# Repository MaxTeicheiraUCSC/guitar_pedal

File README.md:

# guitar_pedal — DSP multi-effect (tremolo · delay · reverb · fuzz)

Daisy Seed3 + ESP32-C3 stereo pedal with a reorderable four-effect chain, five
momentary footswitches, a shared six-knob bank, global high/low-cut toggles, and
BLE-MIDI / WiFi web-UI control. Design rationale, research and the phased plan are
in [`docs/design.md`](docs/design.md); the control protocol in [`docs/midi-map.md`](docs/midi-map.md).

```
firmware/dsp/      portable DSP core (header-only C++17) — shared by the pedal and the emulator
firmware/daisy/    Seed3 wrapper: audio callback, switches, knobs, UART-MIDI, presets   [unverified: no ARM toolchain here]
firmware/esp32/    C3 bridge: BLE-MIDI + WiFi AP web UI ⇄ UART-MIDI                   [unverified: no ESP toolchain here]
web/               single-file web UI served by the ESP32
emulator/          macOS emulator: `emu` offline CLI, hardware model, JUCE front panel (Standalone + VST3), tests
hardware/spice/    ngspice reference of the Seed3 instrument I/O stages + validation harness
hardware/kicad/    carrier board (not started)
docs/              design.md, midi-map.md
```

## Build & test (macOS)

```sh
cd emulator && cmake -B build -DCMAKE_BUILD_TYPE=Release && cmake --build build -j8
./build/dsp_tests                                   # 45 property tests
./build/emu --list                                  # parameter tables + CC numbers
./build/emu --in guitar.wav --out fx.wav --enable 0,1,2,3 --order 3,0,1,2 --hw --cpu
cmake -B build-juce -DPEDAL_BUILD_JUCE=ON && cmake --build build-juce -j8   # JUCE app + VST3 (fetches JUCE 8.0.9)
cmake -B build-juce -DPEDAL_BUILD_JUCE=ON -DPEDAL_HARNESS=ON && ./build-juce/juce/PedalHarness_artefacts/Release/PedalHarness   # in-process UI/audio stress test
cd ../hardware/spice/validate && python3 run_all.py # simple model vs ngspice → out/report.md
```

Handover: **[`docs/STATUS.md`](docs/STATUS.md)** (what is and is not verified, next steps) and
**[`docs/LEARNINGS.md`](docs/LEARNINGS.md)** (the non-obvious things this cost time to find).

## Status (2026-09-22)

- DSP core, emulator CLI, property tests, SPICE reference and validation harness: **done and passing**.
- Validation found and fixed a real error in the hand-derived analog model (input gain −6.2 dB, not −4.6 dB)
  and shows the codec's ±1.8 V limit is reached at ≈3.7 V pk at the jack, before the op-amps clip
  → the carrier board gets Schottky clamps at the codec input.
- JUCE front panel: builds Standalone + VST3 (AU needs full Xcode). Default source is an embedded CC0 clean-guitar loop (`emulator/assets`), so no interface is needed to audition; live input is a menu choice. `PedalHarness` drives the real processor + editor with concurrent audio at 44.1/48/96 kHz and passes.
- Daisy / ESP32 firmware: written, **not compiled** (toolchains not installed on this machine).
- KiCad carrier board: generated from one netlist, routed, 0 DRC errors with schematic parity; gerbers/STEP/BOM in `hardware/kicad/out/`.
- Windows VST3 v0.1.3 links the CRT statically and ships an installer — earlier builds needed the VC++ redistributable and failed to load without it.
- Hardware: nothing fabricated. First hardware task is the Phase A bench measurement in `docs/design.md` §11.
- A project guard (`.claude/settings.json` + `.claude/hooks/guard.py`) confines Claude Code sessions in this repo to this repo; see `docs/STATUS.md`.

## Windows / macOS binaries

`.github/workflows/build.yml` builds the emulator on `windows-latest` (MSVC) and `macos-latest`, runs the
DSP tests, and uploads `PedalEmu-windows-x64.zip` (installer + PedalEmu.vst3 + standalone) and the setup .exe and `PedalEmu-macos.zip`
as workflow artifacts; pushing a tag `v*` publishes them as a GitHub Release. Windows install/troubleshooting: `docs/WINDOWS-INSTALL.md`. The Windows job also builds an
Inno Setup installer, checks the binaries have no dynamic MSVC-runtime dependency, and re-validates
the plugin after extracting the shipped zip. Local Windows build:
`cd emulator && cmake -B build -DPEDAL_BUILD_JUCE=ON && cmake --build build --config Release --target PedalEmu_Standalone PedalEmu_VST3`
(Visual Studio 2022 Build Tools; JUCE 8.0.9 is fetched by CMake). The Windows build has only been
exercised in CI — see the Actions tab for the current status.

License: GPLv3 (see `LICENSE`) — this is the free JUCE tier and permits the GPL reverb algorithms.

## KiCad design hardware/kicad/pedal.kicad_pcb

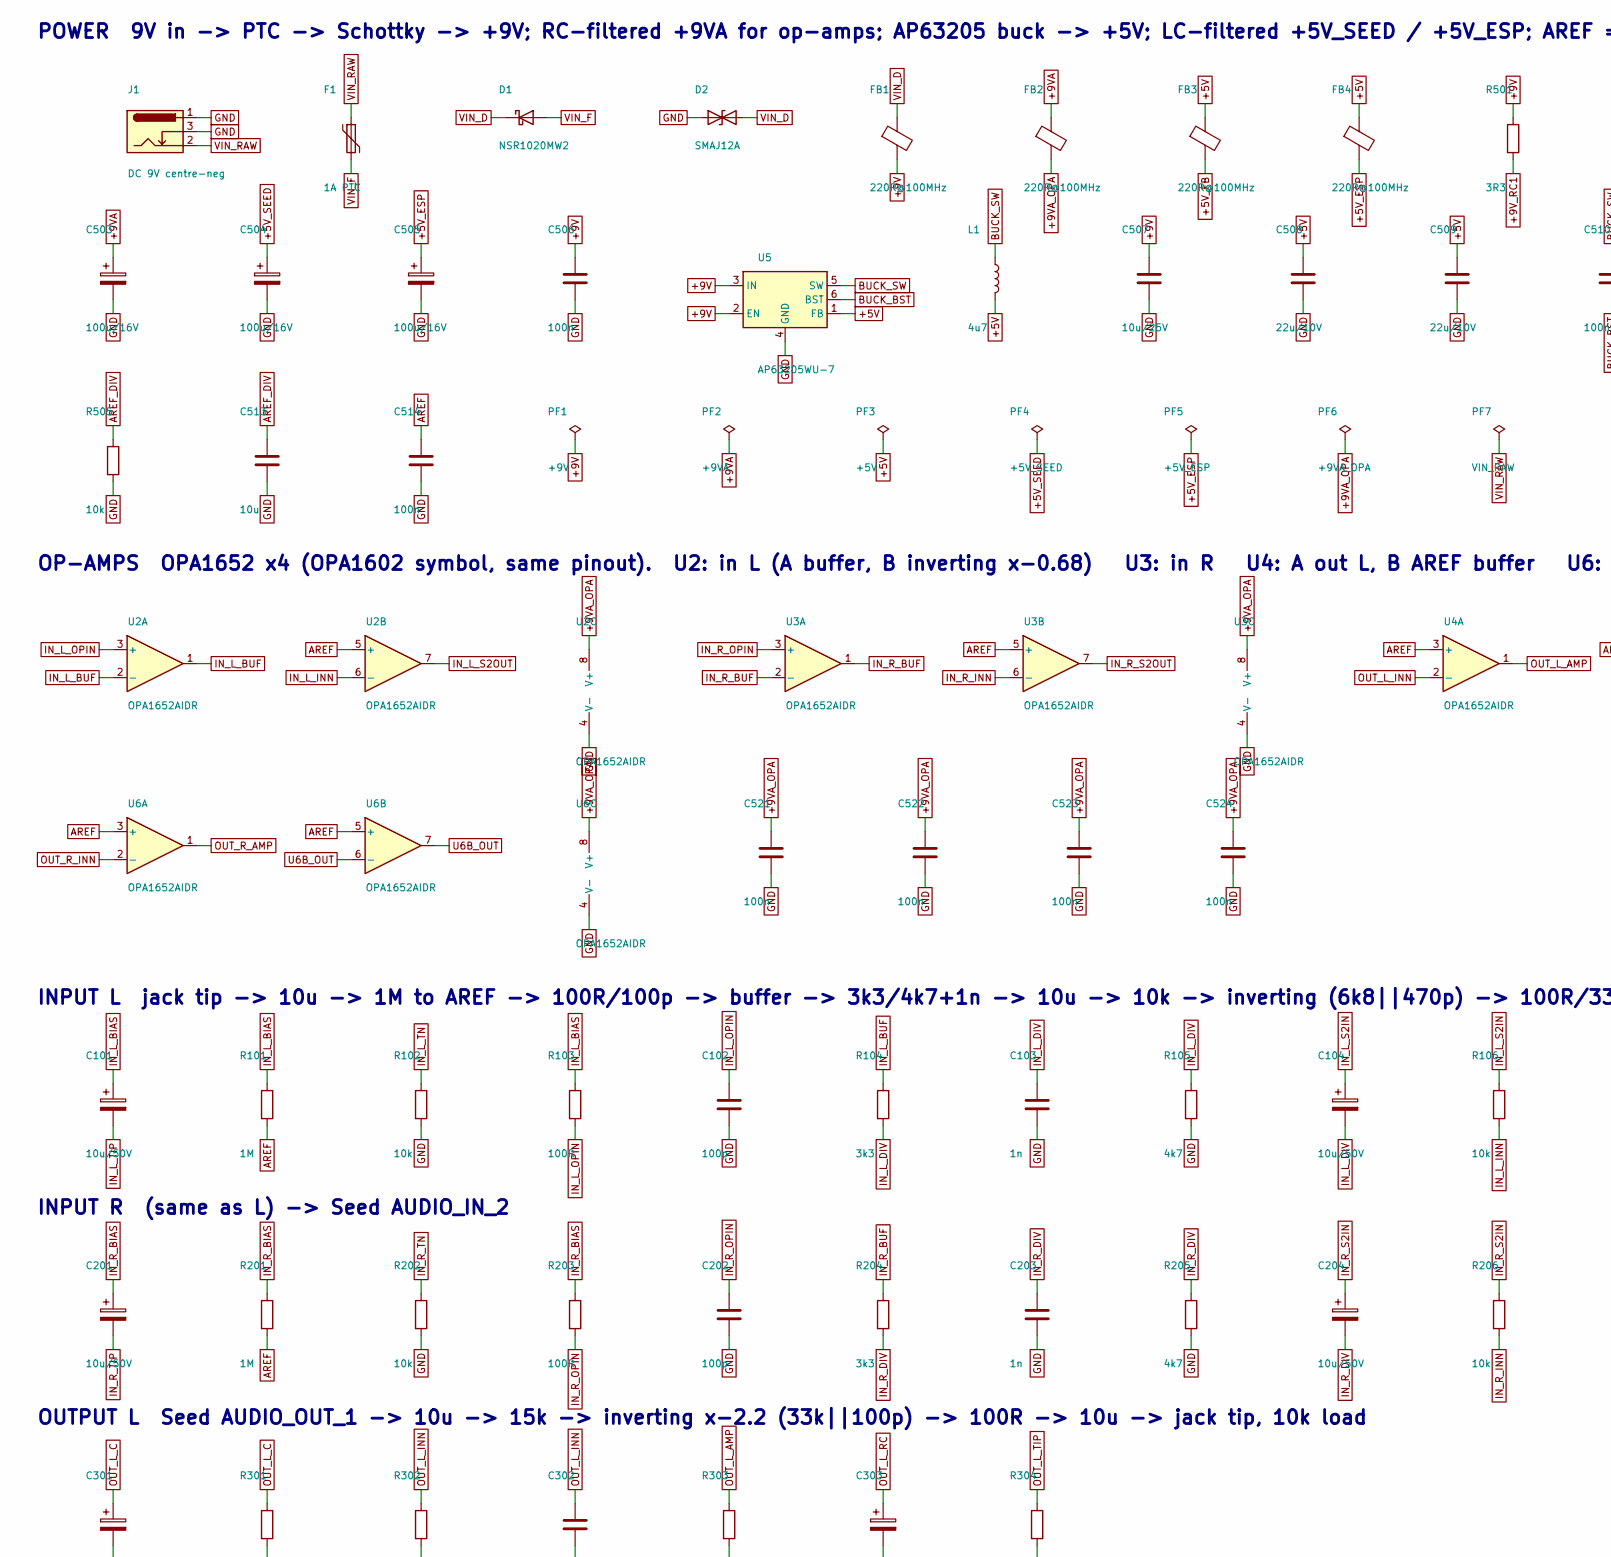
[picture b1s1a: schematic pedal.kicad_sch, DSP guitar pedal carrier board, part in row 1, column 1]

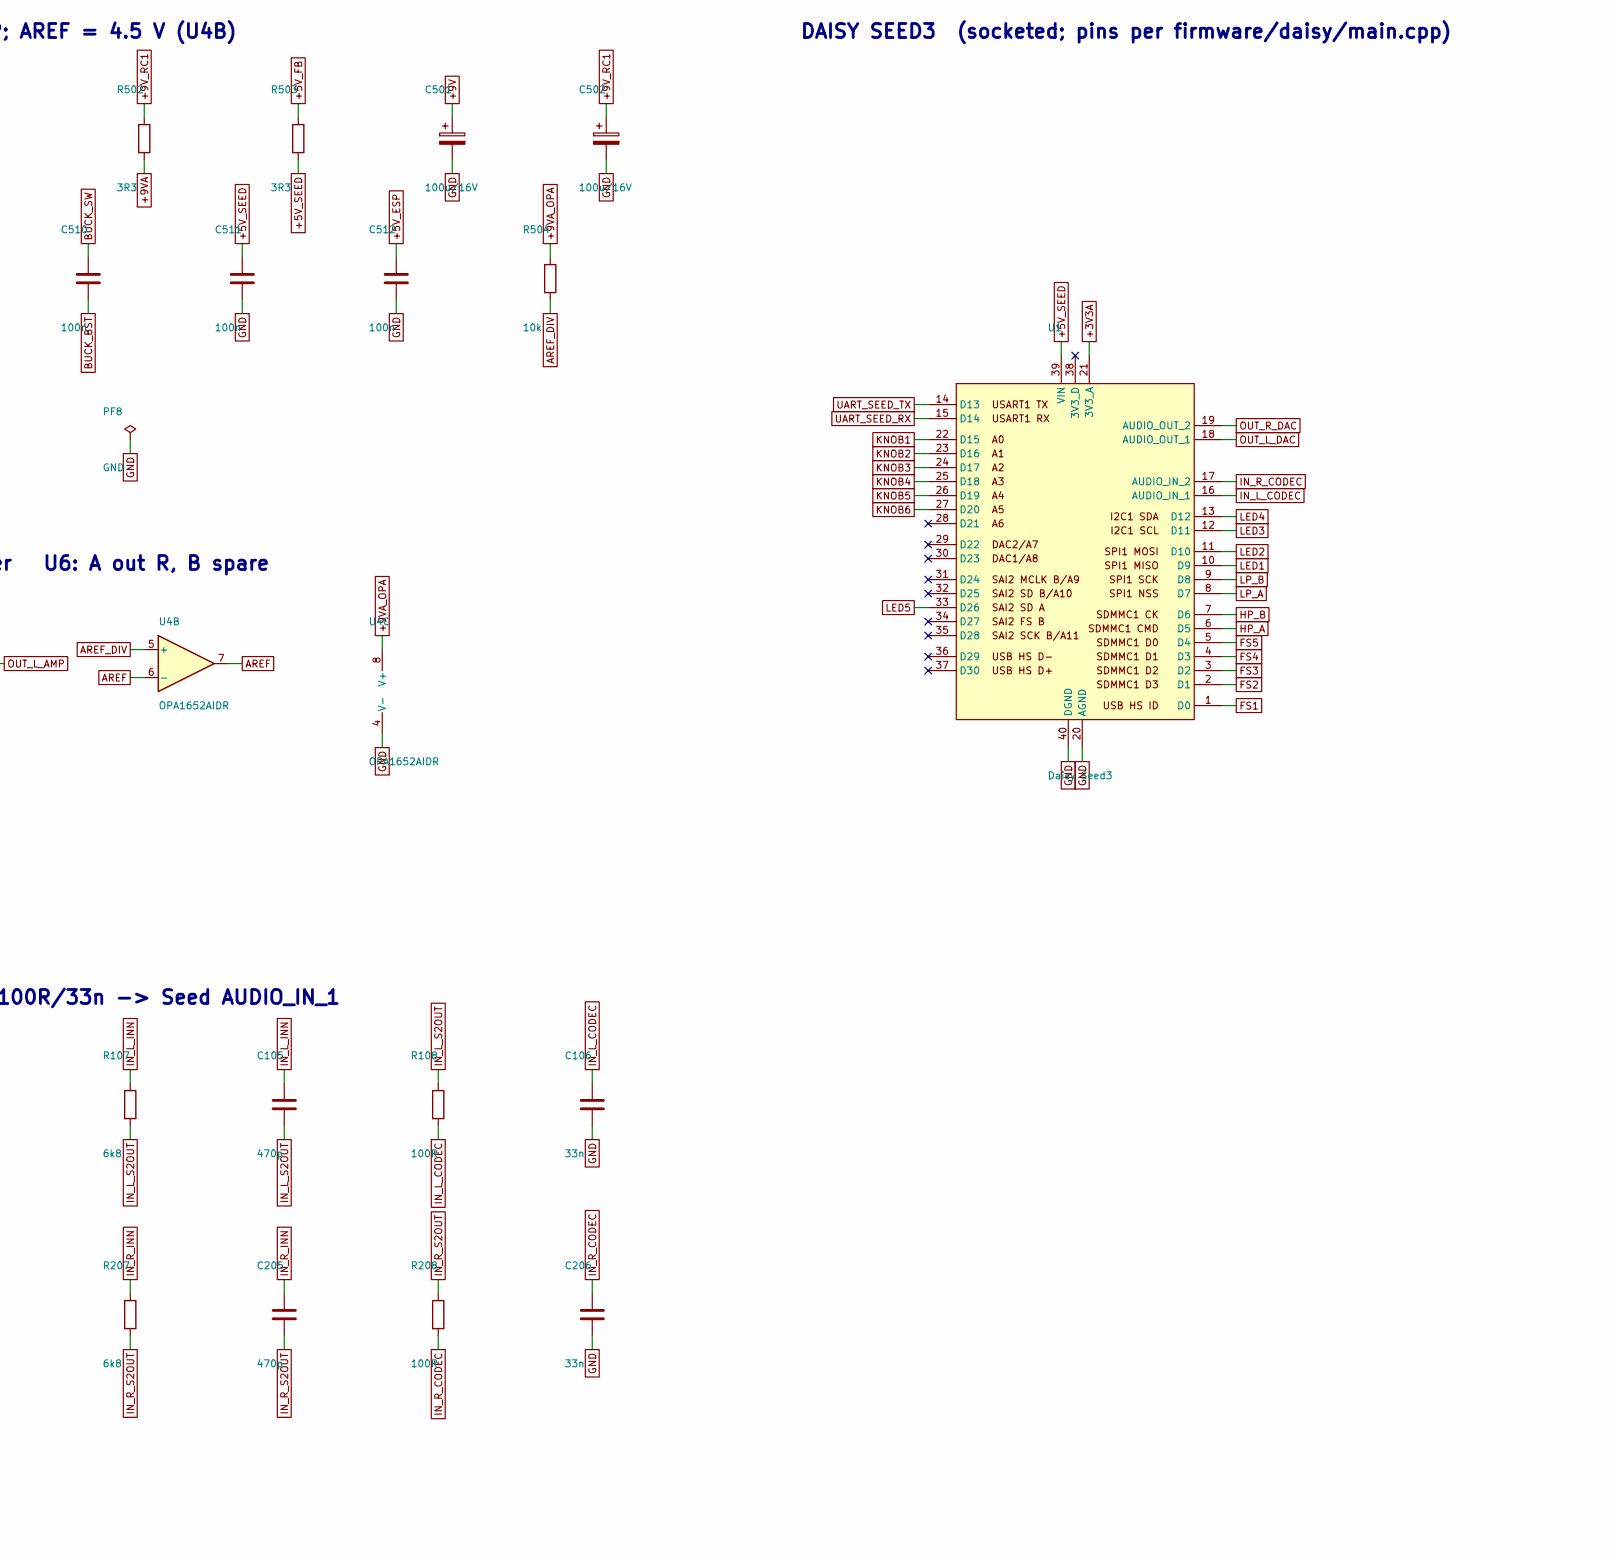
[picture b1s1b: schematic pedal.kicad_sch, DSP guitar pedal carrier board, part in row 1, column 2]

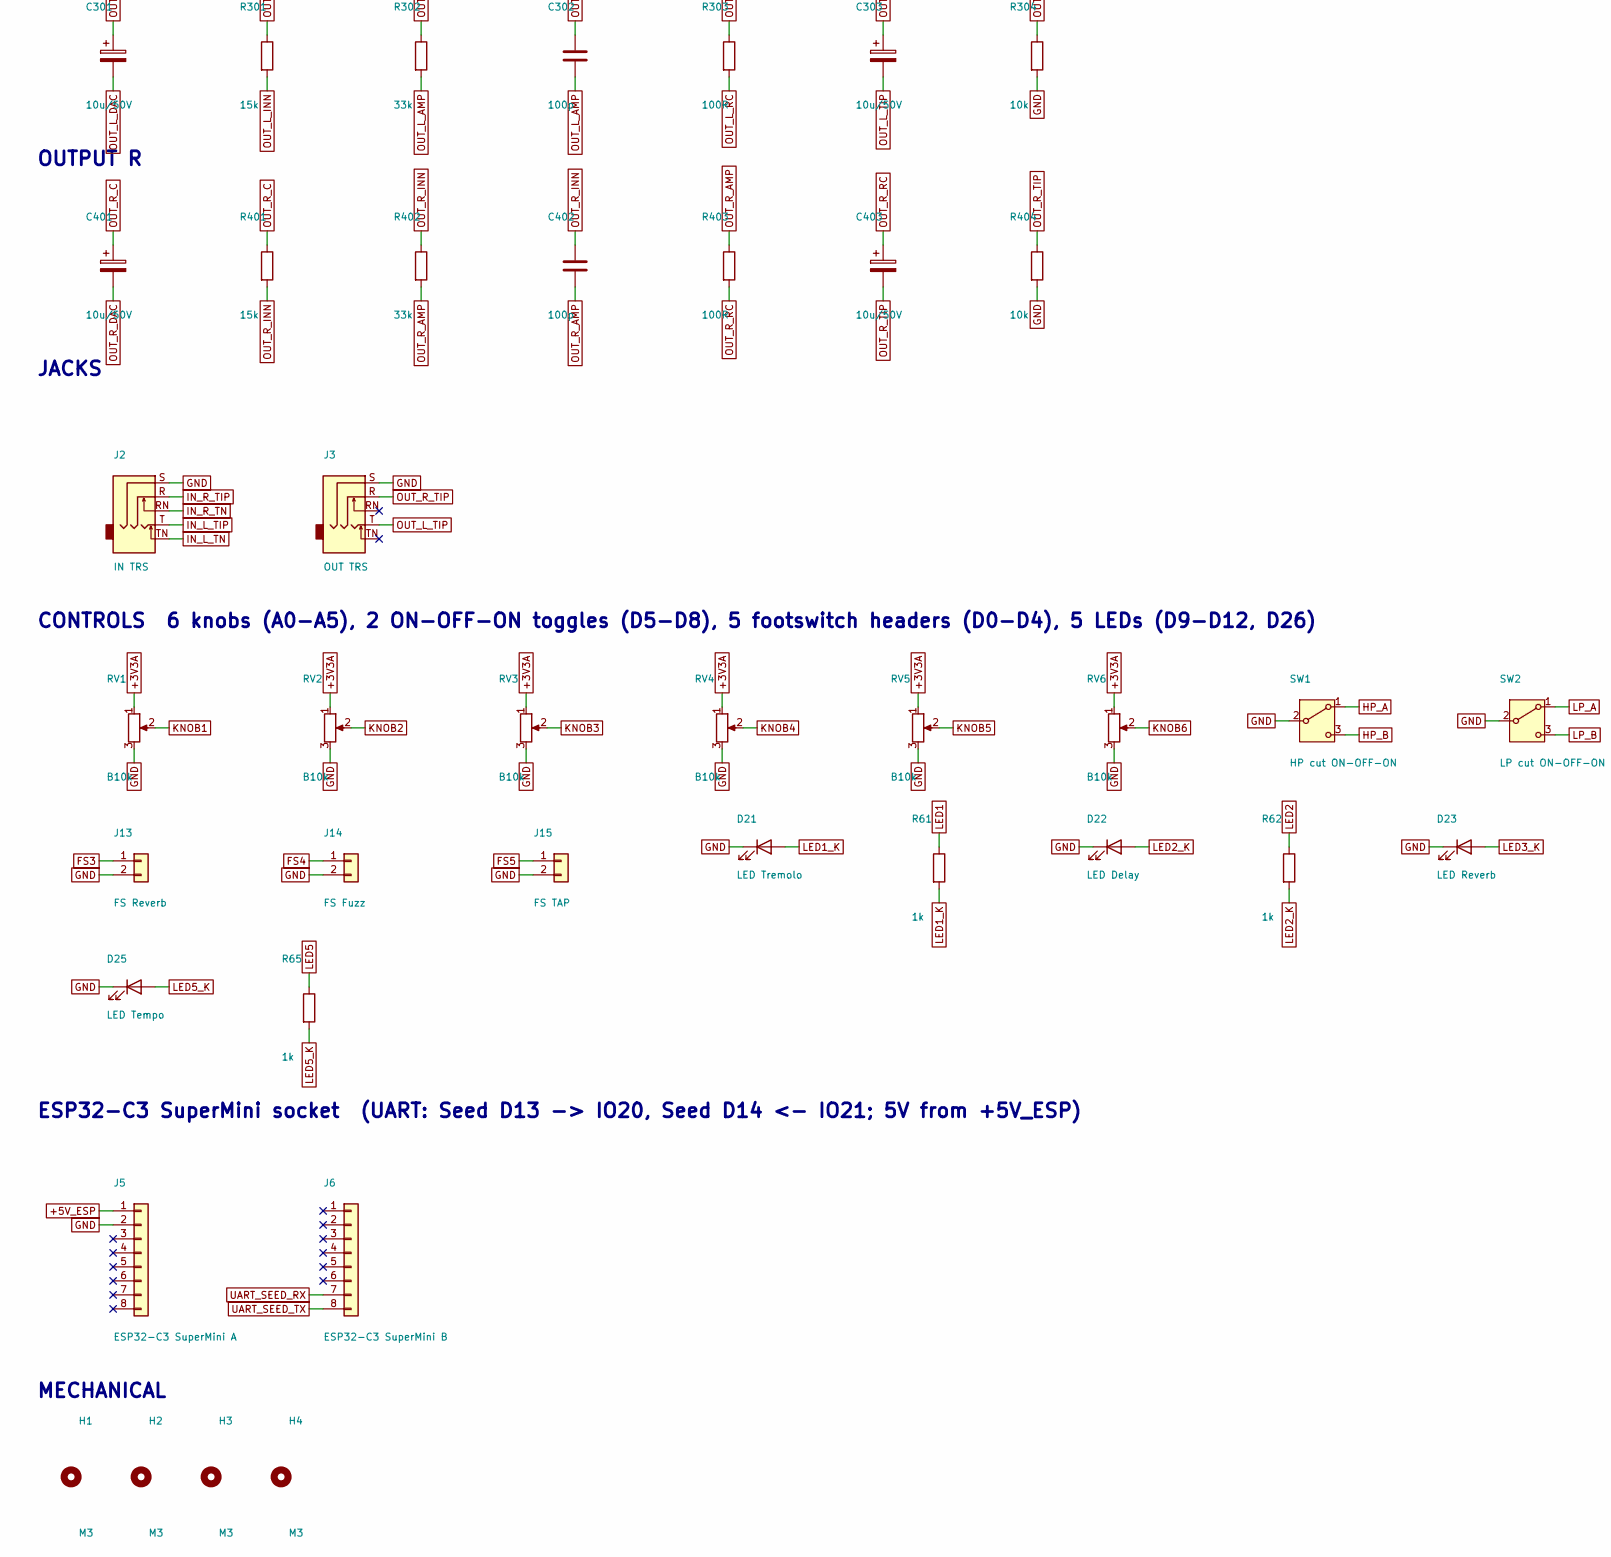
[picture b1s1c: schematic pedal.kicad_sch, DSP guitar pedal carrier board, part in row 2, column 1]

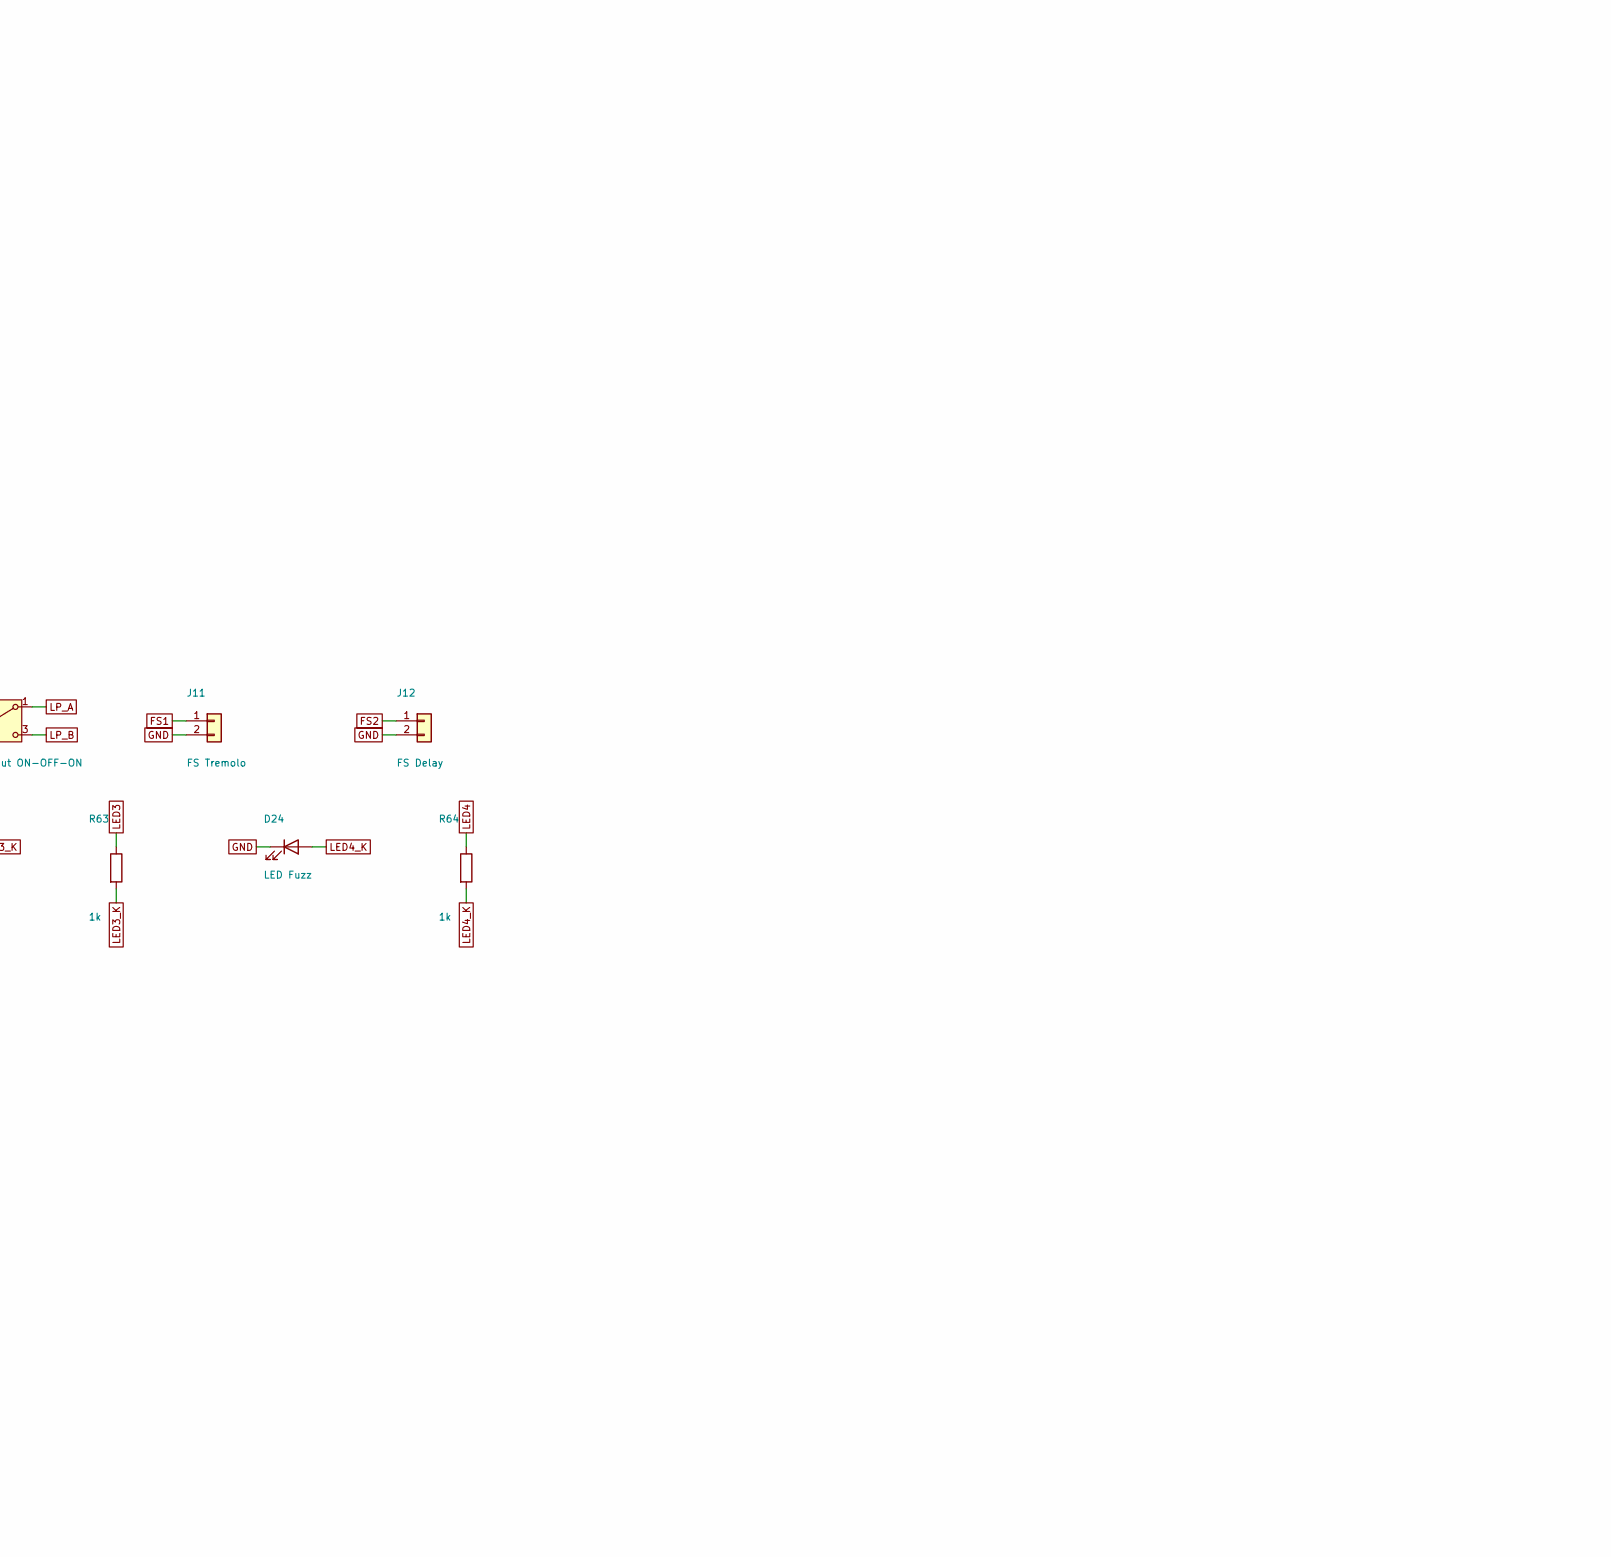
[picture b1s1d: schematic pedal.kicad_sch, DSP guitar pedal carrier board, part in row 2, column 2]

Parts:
C101, C104, C201, C204, C301, C303, C401, C403: 10u/50V; CP_Radial_D5.0mm_P2.00mm
C102, C202, C302, C402: 100p; C_0805_2012Metric
C103, C203: 1n; C_0805_2012Metric
C105, C205: 470p; C_0805_2012Metric
C106, C206: 33n; C_0805_2012Metric
C501, C502, C503, C504, C505: 100u/16V; CP_Radial_D6.3mm_P2.50mm
C506, C511, C512, C514, C521, C522, C523, C524: 100n; C_0805_2012Metric
C507: 10u/25V; C_0805_2012Metric
C508, C509: 22u/10V; C_0805_2012Metric
C510: 100n; C_0603_1608Metric
C513: 10u; C_0805_2012Metric
D1: NSR1020MW2; D_SOD-323; MPN onsemi NSR1020MW2T3G
D2: SMAJ12A; D_SMA; MPN Littelfuse SMAJ12A
D21: LED Tremolo; LED_D3.0mm
D22: LED Delay; LED_D3.0mm
D23: LED Reverb; LED_D3.0mm
D24: LED Fuzz; LED_D3.0mm
D25: LED Tempo; LED_D3.0mm
F1: 1A PTC; Fuse_1812_4532Metric; MPN Bourns MF-MSMF110-2
FB1, FB2, FB3, FB4: 220R@100MHz; L_0805_2012Metric; MPN Murata BLM21PG221SN1D
H1, H2, H3, H4: M3; MountingHole_3.2mm_M3
J1: DC 9V centre-neg; BarrelJack_Horizontal; MPN CUI PJ-102AH or Lumberg 1613 09
J2: IN TRS; Jack_6.35mm_Neutrik_NMJ6HCD2_Horizontal; MPN Neutrik NMJ6HCD2
J3: OUT TRS; Jack_6.35mm_Neutrik_NMJ6HCD2_Horizontal; MPN Neutrik NMJ6HCD2
J5: ESP32-C3 SuperMini A; PinSocket_1x08_P2.54mm_Vertical
J6: ESP32-C3 SuperMini B; PinSocket_1x08_P2.54mm_Vertical
J11: FS Tremolo; JST_XH_B2B-XH-A_1x02_P2.50mm_Vertical; MPN JST B2B-XH-A
J12: FS Delay; JST_XH_B2B-XH-A_1x02_P2.50mm_Vertical; MPN JST B2B-XH-A
J13: FS Reverb; JST_XH_B2B-XH-A_1x02_P2.50mm_Vertical; MPN JST B2B-XH-A
J14: FS Fuzz; JST_XH_B2B-XH-A_1x02_P2.50mm_Vertical; MPN JST B2B-XH-A
J15: FS TAP; JST_XH_B2B-XH-A_1x02_P2.50mm_Vertical; MPN JST B2B-XH-A
L1: 4u7; L_Bourns_SRN6045TA; MPN Bourns SRN6045TA-4R7M
PF1: +9V
PF2: +9VA
PF3: +5V
PF4: +5V_SEED
PF5: +5V_ESP
PF6: +9VA_OPA
PF7: VIN_RAW
PF8: GND
R61, R62, R63, R64, R65: 1k; R_0805_2012Metric
R101, R201: 1M; R_0805_2012Metric
R102, R106, R202, R206, R304, R404, R504, R505: 10k; R_0805_2012Metric
R103, R108, R203, R208, R303, R403: 100R; R_0805_2012Metric
R104, R204: 3k3; R_0805_2012Metric
R105, R205: 4k7; R_0805_2012Metric
R107, R207: 6k8; R_0805_2012Metric
R301, R401: 15k; R_0805_2012Metric
R302, R402: 33k; R_0805_2012Metric
R501, R502, R503: 3R3; R_1206_3216Metric
RV1, RV2, RV3, RV4, RV5, RV6: B10k; Potentiometer_Alpha_RD901F-40-00D_Single_Vertical; MPN Alpha RD901F-40-15F-B10K
SW1: HP cut ON-OFF-ON; SW_Toggle_2M_SPDT_Vertical; MPN Dailywell 2MS3T1B1M2QES
SW2: LP cut ON-OFF-ON; SW_Toggle_2M_SPDT_Vertical; MPN Dailywell 2MS3T1B1M2QES
U1: Daisy Seed3; DAISY_SEED; MPN Electro-Smith Seed3
U2, U3, U4, U6: OPA1652AIDR; SOIC-8_3.9x4.9mm_P1.27mm; MPN TI OPA1652AIDR
U5: AP63205WU-7; TSOT-23-6; MPN Diodes AP63205WU-7

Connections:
+3V3A: RV1.1, RV2.1, RV3.1, RV4.1, RV5.1, RV6.1, U1.21 (3V3_A)
+5V: C508.1, C509.1, FB3.1, FB4.1, L1.2, PF3.1, U5.1 (FB)
+5V_ESP: C505.1, C512.1, FB4.2, J5.1, PF5.1
+5V_FB: FB3.2, R503.1
+5V_SEED: C504.1, C511.1, PF4.1, R503.2, U1.39 (VIN)
+9V: C501.1, C506.1, C507.1, FB1.2, PF1.1, R501.1, U5.2 (EN), U5.3 (IN)
+9VA: C503.1, FB2.1, PF2.1, R502.2
+9VA_OPA: C521.1, C522.1, C523.1, C524.1, FB2.2, PF6.1, R504.1, U2.8 (V+), U3.8 (V+), U4.8 (V+), U6.8 (V+)
+9V_RC1: C502.1, R501.2, R502.1
AREF: C514.1, R101.2, R201.2, U2.5 (+), U3.5 (+), U4.3 (+), U4.6 (-), U4.7, U6.3 (+), U6.5 (+)
AREF_DIV: C513.1, R504.2, R505.1, U4.5 (+)
BUCK_BST: C510.2, U5.6 (BST)
BUCK_SW: C510.1, L1.1, U5.5 (SW)
FS1: J11.1, U1.1 (D0)
FS2: J12.1, U1.2 (D1)
FS3: J13.1, U1.3 (D2)
FS4: J14.1, U1.4 (D3)
FS5: J15.1, U1.5 (D4)
GND: C102.2, C103.2, C106.2, C202.2, C203.2, C206.2, C501.2, C502.2, C503.2, C504.2, C505.2, C506.2, C507.2, C508.2, C509.2, C511.2, C512.2, C513.2, C514.2, C521.2, C522.2, C523.2, C524.2, D2.1 (A1), D21.1 (K), D22.1 (K), D23.1 (K), D24.1 (K), D25.1 (K), J1.1, J1.3, J2.S, J3.S, J5.2, J11.2, J12.2, J13.2, J14.2, J15.2, PF8.1, R102.2, R105.2, R202.2, R205.2, R304.2, R404.2, R505.2, RV1.3, RV2.3, RV3.3, RV4.3, RV5.3, RV6.3, SW1.2 (B), SW2.2 (B), U1.20 (AGND), U1.40 (DGND), U2.4 (V-), U3.4 (V-), U4.4 (V-), U5.4 (GND), U6.4 (V-)
HP_A: SW1.1 (A), U1.6 (D5)
HP_B: SW1.3 (C), U1.7 (D6)
IN_L_BIAS: C101.1, R101.1, R103.1
IN_L_BUF: R104.1, U2.1, U2.2 (-)
IN_L_CODEC: C106.1, R108.2, U1.16 (AUDIO_IN_1)
IN_L_DIV: C103.1, C104.2, R104.2, R105.1
IN_L_INN: C105.1, R106.2, R107.1, U2.6 (-)
IN_L_OPIN: C102.1, R103.2, U2.3 (+)
IN_L_S2IN: C104.1, R106.1
IN_L_S2OUT: C105.2, R107.2, R108.1, U2.7
IN_L_TIP: C101.2, J2.T
IN_L_TN: J2.TN, R102.1
IN_R_BIAS: C201.1, R201.1, R203.1
IN_R_BUF: R204.1, U3.1, U3.2 (-)
IN_R_CODEC: C206.1, R208.2, U1.17 (AUDIO_IN_2)
IN_R_DIV: C203.1, C204.2, R204.2, R205.1
IN_R_INN: C205.1, R206.2, R207.1, U3.6 (-)
IN_R_OPIN: C202.1, R203.2, U3.3 (+)
IN_R_S2IN: C204.1, R206.1
IN_R_S2OUT: C205.2, R207.2, R208.1, U3.7
IN_R_TIP: C201.2, J2.R
IN_R_TN: J2.RN, R202.1
KNOB1: RV1.2, U1.22 (D15)
KNOB2: RV2.2, U1.23 (D16)
KNOB3: RV3.2, U1.24 (D17)
KNOB4: RV4.2, U1.25 (D18)
KNOB5: RV5.2, U1.26 (D19)
KNOB6: RV6.2, U1.27 (D20)
LED1: R61.1, U1.10 (D9)
LED1_K: D21.2 (A), R61.2
LED2: R62.1, U1.11 (D10)
LED2_K: D22.2 (A), R62.2
LED3: R63.1, U1.12 (D11)
LED3_K: D23.2 (A), R63.2
LED4: R64.1, U1.13 (D12)
LED4_K: D24.2 (A), R64.2
LED5: R65.1, U1.33 (D26)
LED5_K: D25.2 (A), R65.2
LP_A: SW2.1 (A), U1.8 (D7)
LP_B: SW2.3 (C), U1.9 (D8)
OUT_L_AMP: C302.2, R302.2, R303.1, U4.1
OUT_L_C: C301.1, R301.1
OUT_L_DAC: C301.2, U1.18 (AUDIO_OUT_1)
OUT_L_INN: C302.1, R301.2, R302.1, U4.2 (-)
OUT_L_RC: C303.1, R303.2
OUT_L_TIP: C303.2, J3.T, R304.1
OUT_R_AMP: C402.2, R402.2, R403.1, U6.1
OUT_R_C: C401.1, R401.1
OUT_R_DAC: C401.2, U1.19 (AUDIO_OUT_2)
OUT_R_INN: C402.1, R401.2, R402.1, U6.2 (-)
OUT_R_RC: C403.1, R403.2
OUT_R_TIP: C403.2, J3.R, R404.1
U6B_OUT: U6.6 (-), U6.7
UART_SEED_RX: J6.7, U1.15 (D14)
UART_SEED_TX: J6.8, U1.14 (D13)
VIN_D: D1.1 (K), D2.2 (A2), FB1.1
VIN_F: D1.2 (A), F1.2
VIN_RAW: F1.1, J1.2, PF7.1

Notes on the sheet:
POWER 9V in -> PTC -> Schottky -> +9V; RC-filtered +9VA for op-amps; AP63205 buck -> +5V; LC-filtered +5V_SEED / +5V_ESP; AREF = 4.5 V (U4B)
OP-AMPS OPA1652 x4 (OPA1602 symbol, same pinout). U2: in L (A buffer, B inverting x-0.68) U3: in R U4: A out L, B AREF buffer U6: A out R, B spare
INPUT L jack tip -> 10u -> 1M to AREF -> 100R/100p -> buffer -> 3k3/4k7+1n -> 10u -> 10k -> inverting (6k8||470p) -> 100R/33n -> Seed AUDIO_IN_1
INPUT R (same as L) -> Seed AUDIO_IN_2
OUTPUT L Seed AUDIO_OUT_1 -> 10u -> 15k -> inverting x-2.2 (33k||100p) -> 100R -> 10u -> jack tip, 10k load
OUTPUT R
JACKS
CONTROLS 6 knobs (A0-A5), 2 ON-OFF-ON toggles (D5-D8), 5 footswitch headers (D0-D4), 5 LEDs (D9-D12, D26)
ESP32-C3 SuperMini socket (UART: Seed D13 -> IO20, Seed D14 <- IO21; 5V from +5V_ESP)
MECHANICAL
DAISY SEED3 (socketed; pins per firmware/daisy/main.cpp)

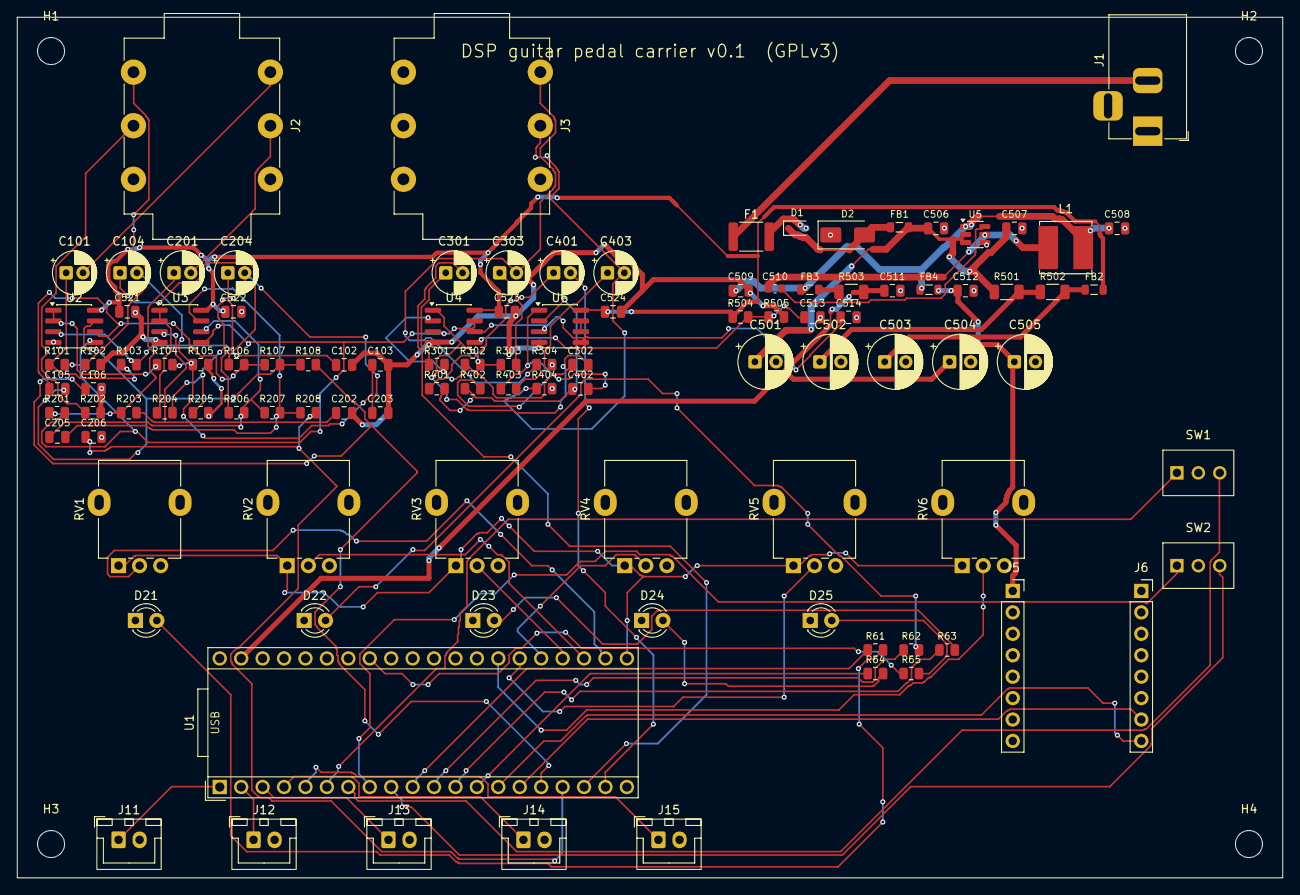
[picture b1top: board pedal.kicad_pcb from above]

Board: 2 copper layers, 150.0 x 102.0 mm, 111 parts (0 on the bottom side), 77 nets.

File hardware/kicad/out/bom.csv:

"Reference","Value","Footprint","MPN","Description"
"C101,C104,C201,C204,C301,C303,C401,C403","10u/50V","Capacitor_THT:CP_Radial_D5.0mm_P2.00mm","","in L coupling,in L stage-2 coupling,in R coupling,in R stage-2 coupling,out L DAC coupling,out L coupling,out R DAC coupling,out R coupling"
"C102,C202,C302,C402","100p","Capacitor_SMD:C_0805_2012Metric","","in L rf,in R rf,out L fb,out R fb"
"C103,C203","1n","Capacitor_SMD:C_0805_2012Metric","","in L divider lp,in R divider lp"
"C105,C205","470p","Capacitor_SMD:C_0805_2012Metric","","in L stage-2 fb (~50 kHz),in R stage-2 fb (~50 kHz)"
"C106,C206","33n","Capacitor_SMD:C_0805_2012Metric","","in L codec lp,in R codec lp"
"C501-C505","100u/16V","Capacitor_THT:CP_Radial_D6.3mm_P2.50mm","","rail bulk"
"C506,C511,C512,C514,C521-C524","100n","Capacitor_SMD:C_0805_2012Metric","","+5V_ESP hf,+5V_SEED hf,+9V hf,AREF out hf,U2 decoupling,U3 decoupling,U4 decoupling,U6 decoupling"
"C507","10u/25V","Capacitor_SMD:C_0805_2012Metric","","buck Cin"
"C508,C509","22u/10V","Capacitor_SMD:C_0805_2012Metric","","buck Cout"
"C510","100n","Capacitor_SMD:C_0603_1608Metric","","buck BST"
"C513","10u","Capacitor_SMD:C_0805_2012Metric","","AREF divider filter"
"D1","NSR1020MW2","Diode_SMD:D_SOD-323","onsemi NSR1020MW2T3G","reverse polarity, SOD-323"
"D2","SMAJ12A","Diode_SMD:D_SMA","Littelfuse SMAJ12A","surge clamp"
"D21","LED Tremolo","LED_THT:LED_D3.0mm","","3 mm"
"D22","LED Delay","LED_THT:LED_D3.0mm","","3 mm"
"D23","LED Reverb","LED_THT:LED_D3.0mm","","3 mm"
"D24","LED Fuzz","LED_THT:LED_D3.0mm","","3 mm"
"D25","LED Tempo","LED_THT:LED_D3.0mm","","3 mm"
"F1","1A PTC","Fuse:Fuse_1812_4532Metric","Bourns MF-MSMF110-2","resettable fuse"
"FB1-FB4","220R@100MHz","Inductor_SMD:L_0805_2012Metric","Murata BLM21PG221SN1D","ESP32 5V bead,Seed 5V bead,analog rail bead,input bead"
"J1","DC 9V centre-neg","Connector_BarrelJack:BarrelJack_Horizontal","CUI PJ-102AH or Lumberg 1613 09","2.1 mm barrel; pedal standard: sleeve = +9 V, centre = 0 V"
"J2","IN TRS","Connector_Audio:Jack_6.35mm_Neutrik_NMJ6HCD2_Horizontal","Neutrik NMJ6HCD2","input, TS = mono"
"J3","OUT TRS","Connector_Audio:Jack_6.35mm_Neutrik_NMJ6HCD2_Horizontal","Neutrik NMJ6HCD2","output"
"J5","ESP32-C3 SuperMini A","Connector_PinSocket_2.54mm:PinSocket_1x08_P2.54mm_Vertical","","left row: 5V GND 3V3 IO0 IO1 IO2 IO3 IO4"
"J6","ESP32-C3 SuperMini B","Connector_PinSocket_2.54mm:PinSocket_1x08_P2.54mm_Vertical","","right row: IO5 IO6 IO7 IO8 IO9 IO10 IO21 IO20"
"J11","FS Tremolo","Connector_JST:JST_XH_B2B-XH-A_1x02_P2.50mm_Vertical","JST B2B-XH-A","to SPST momentary footswitch"
"J12","FS Delay","Connector_JST:JST_XH_B2B-XH-A_1x02_P2.50mm_Vertical","JST B2B-XH-A","to SPST momentary footswitch"
"J13","FS Reverb","Connector_JST:JST_XH_B2B-XH-A_1x02_P2.50mm_Vertical","JST B2B-XH-A","to SPST momentary footswitch"
"J14","FS Fuzz","Connector_JST:JST_XH_B2B-XH-A_1x02_P2.50mm_Vertical","JST B2B-XH-A","to SPST momentary footswitch"
"J15","FS TAP","Connector_JST:JST_XH_B2B-XH-A_1x02_P2.50mm_Vertical","JST B2B-XH-A","to SPST momentary footswitch"
"L1","4u7","Inductor_SMD:L_Bourns_SRN6045TA","Bourns SRN6045TA-4R7M","buck inductor"
"R61-R65","1k","Resistor_SMD:R_0805_2012Metric","","LED Delay series,LED Fuzz series,LED Reverb series,LED Tempo series,LED Tremolo series"
"R101,R201","1M","Resistor_SMD:R_0805_2012Metric","","in L bias,in R bias"
"R102,R106,R202,R206,R304,R404,R504,R505","10k","Resistor_SMD:R_0805_2012Metric","","AREF divider,in L stage-2 in,in L tip-normal pull-down,in R stage-2 in,in R tip-normal pull-down,out L load,out R load"
"R103,R108,R203,R208,R303,R403","100R","Resistor_SMD:R_0805_2012Metric","","in L codec series,in L rf,in R codec series,in R rf,out L series,out R series"
"R104,R204","3k3","Resistor_SMD:R_0805_2012Metric","","in L divider,in R divider"
"R105,R205","4k7","Resistor_SMD:R_0805_2012Metric","","in L divider,in R divider"
"R107,R207","6k8","Resistor_SMD:R_0805_2012Metric","","in L stage-2 fb (gain 0.68: codec never exceeds 1.8 V),in R stage-2 fb (gain 0.68: codec never exceeds 1.8 V)"
"R301,R401","15k","Resistor_SMD:R_0805_2012Metric","","out L in,out R in"
"R302,R402","33k","Resistor_SMD:R_0805_2012Metric","","out L fb,out R fb"
"R501-R503","3R3","Resistor_SMD:R_1206_3216Metric","","rail RC filter"
"RV1-RV6","B10k","Potentiometer_THT:Potentiometer_Alpha_RD901F-40-00D_Single_Vertical","Alpha RD901F-40-15F-B10K","knob 1,knob 2,knob 3,knob 4,knob 5,knob 6"
"SW1","HP cut ON-OFF-ON","pedal:SW_Toggle_2M_SPDT_Vertical","Dailywell 2MS3T1B1M2QES","global high-cut toggle"
"SW2","LP cut ON-OFF-ON","pedal:SW_Toggle_2M_SPDT_Vertical","Dailywell 2MS3T1B1M2QES","global low-cut toggle"
"U1","Daisy Seed3","Daisy-Boards:DAISY_SEED","Electro-Smith Seed3","DSP board, socketed (2x 1x20 female headers)"
"U2-U4,U6","OPA1652AIDR","Package_SO:SOIC-8_3.9x4.9mm_P1.27mm","TI OPA1652AIDR","A output L, B AREF buffer,A output R, B spare follower,input L: A buffer, B inverting,input R: A buffer, B inverting"
"U5","AP63205WU-7","Package_TO_SOT_SMD:TSOT-23-6","Diodes AP63205WU-7","9V->5V buck 2A"

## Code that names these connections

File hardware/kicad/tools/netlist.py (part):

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        N[name].append((ref, str(pin)))

# power path: jack sleeve (+9) -> PTC -> Schottky -> bead -> +9V
net("VIN_RAW", ("J1", "2"), ("F1", "1"), ("PF7", "1"))
net("VIN_F", ("F1", "2"), ("D1", "2"))              # D1 anode
net("VIN_D", ("D1", "1"), ("FB1", "1"), ("D2", "2"))  # D1 cathode; TVS across it
net("+9V", ("FB1", "2"), ("C501", "1"), ("C506", "1"), ("R501", "1"), ("U5", "3"), ("U5", "2"), ("C507", "1"), ("PF1", "1"))
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net("HP_A", ("SW1", "1"), ("U1", "6")); net("HP_B", ("SW1", "3"), ("U1", "7"))      # D5, D6
net("LP_A", ("SW2", "1"), ("U1", "8")); net("LP_B", ("SW2", "3"), ("U1", "9"))      # D7, D8
for i in range(1, 5): net(f"LED{i}", ("U1", str(9 + i)), (f"R6{i}", "1")); net(f"LED{i}_K", (f"R6{i}", "2"), (f"D2{i}", "2"))   # D9..D12 = pins 10..13
net("LED5", ("U1", "33"), ("R65", "1")); net("LED5_K", ("R65", "2"), ("D25", "2"))                                                 # D26 = pin 33
# UART: Seed D13 (pin 14, TX) -> C3 IO20 (J6.8, RX); Seed D14 (pin 15, RX) <- C3 IO21 (J6.7, TX)
net("UART_SEED_TX", ("U1", "14"), ("J6", "8"))
net("UART_SEED_RX", ("U1", "15"), ("J6", "7"))
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

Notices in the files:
hardware/kicad/pedal.kicad_pcb:
DSP guitar pedal carrier v0.1  (GPLv3)
